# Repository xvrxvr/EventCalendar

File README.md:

# EventCalendar
Event Calendar Project

This project is a custom hardware device (with an ESP32 microcontroller, an LCD, a fingerprint sensor, and a bunch of solenoids that are used as control locks for a set of small doors)
Each door closes a separate box with some kind of gift.
The user must solve some kind of puzzle to open the door.

## Project Contents

Directory Contents:

* 3D contains a 3D model for the panel around the LCD
* sch - Schematic. The PCB version is outdated at this point (some schematic changes were made after the PCB was provided). There are also 2 schematics:
  * **ev_cal** - The calendar itself
  * **vboost** - Voltage boost for the solenoids (it is connected instead of L1)
* soft - Software. 6 directories included:
  * expr_quest - Prototype (in Python) for benchmark testing
  * firmware - Firmware (VS Code + IDF plugin)
  * sg - Character generator scripts
  * tst - Hardware test (VS Code + IDF plugin)
  * bloader - OTA loader (OTA is also supported in the main software)
  * ext_logger - External logger client. The external logging system is currently under development. It allows forwarding all internal UART messages to a remote TCP server. This system (with OTA capability) allows creating and debugging new software versions without special software hardware.
* spice - Spice mode for the voltage amplifier

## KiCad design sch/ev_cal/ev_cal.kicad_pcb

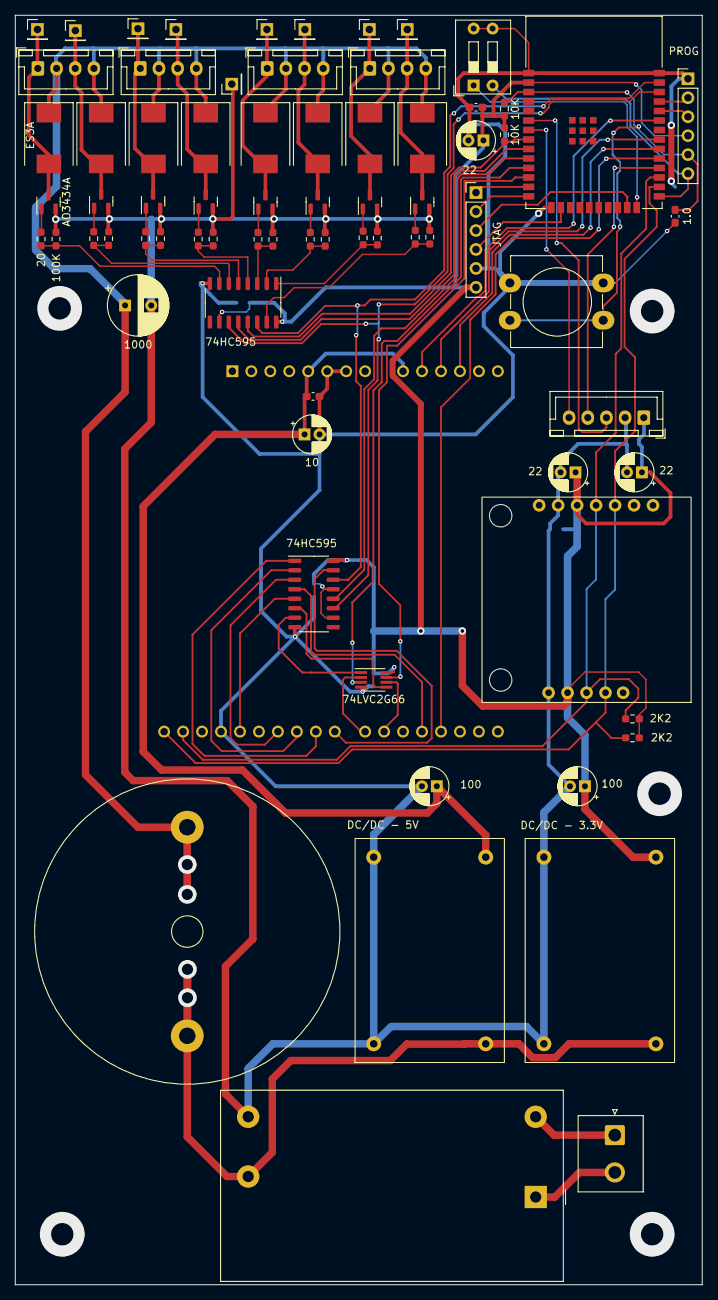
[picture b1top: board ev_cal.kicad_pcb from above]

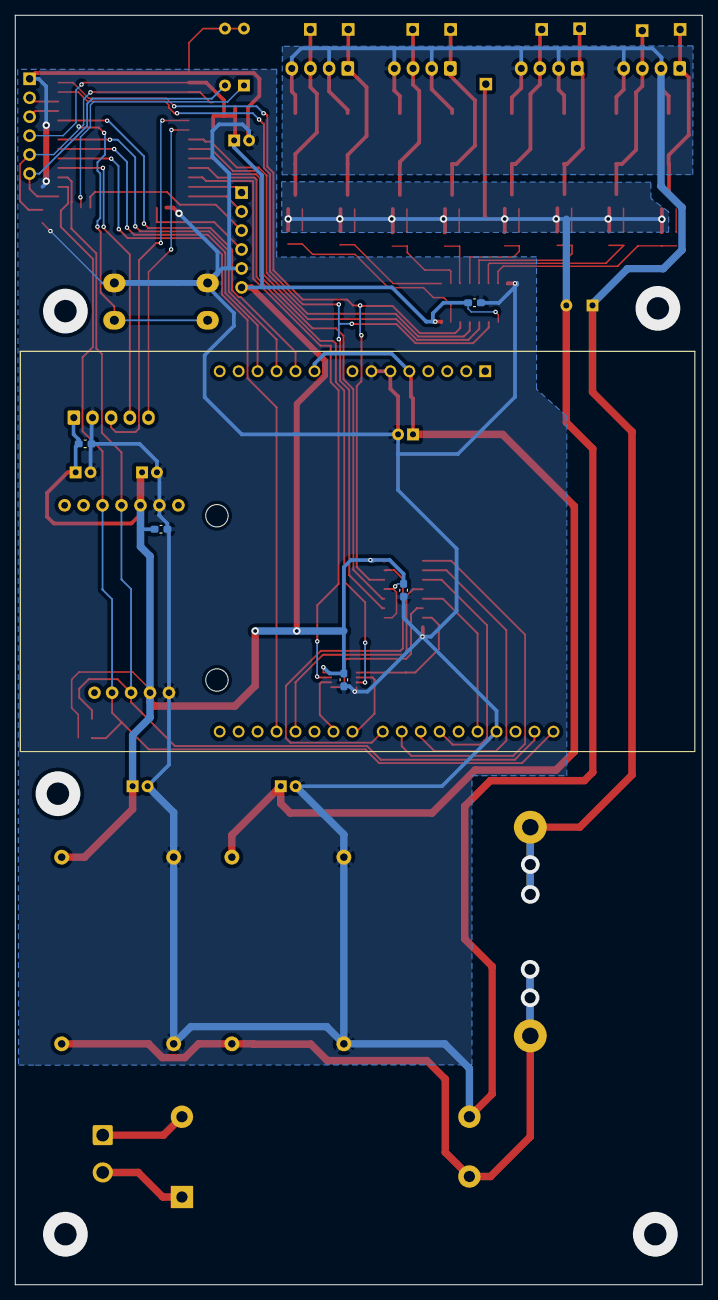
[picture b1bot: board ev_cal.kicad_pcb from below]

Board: 2 copper layers, 92.0 x 170.0 mm, 80 parts (6 on the bottom side), 66 nets.

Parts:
C1: 10; CP_Radial_D5.0mm_P2.00mm
C2, C7, C10: 22; CP_Radial_D5.0mm_P2.00mm
C3, C9, C11, C12, C13, C14, C15: 0.1; C_0603_1608Metric_Pad1.08x0.95mm_HandSolder
C4: 1.0; C_0603_1608Metric_Pad1.08x0.95mm_HandSolder
C5, C6: 100; CP_Radial_D5.0mm_P2.00mm
C8: 1000; CP_Radial_D8.0mm_P3.50mm
D1, D2, D3, D4, D5, D6, D7, D8: ES3A; D_SMC
J1: JTAG; PinHeader_1x06_P2.54mm_Vertical
J2: PROG; PinHeader_1x06_P2.54mm_Vertical
J3, J4, J5, J6: Conn_01x04_Male; JST_XH_B4B-XH-A_1x04_P2.50mm_Vertical
J11: Conn_01x01_Male; PinHeader_1x01_P2.54mm_Vertical
J12, J13, J14, J15, J16, J17, J18, J19: Conn_01x01_Female; PinHeader_1x01_P2.54mm_Vertical
L1: 10mH; L_Radial_D40.6mm_P27.94mm_Vishay_IHB-4
P1: Conn_WallPlug; JST_NV_B02P-NV_1x02_P5.00mm_Vertical
PS1: IRM-10-12; Converter_ACDC_MeanWell_IRM-10-xx_THT
Q1, Q2, Q3, Q4, Q5, Q6, Q7, Q8: AO3434A; SOT-23
R1, R2: 10K; R_0603_1608Metric_Pad0.98x0.95mm_HandSolder
R3, R4: 2K2; R_0603_1608Metric_Pad0.98x0.95mm_HandSolder
R5, R7, R9, R11, R13, R15, R17, R19: 100K; R_0603_1608Metric_Pad0.98x0.95mm_HandSolder
R6, R8, R10, R12, R14, R16, R18, R20: 20; R_0603_1608Metric_Pad0.98x0.95mm_HandSolder
SW1: SW_Push; SW_PUSH-12mm_Wuerth-430476085716
SW2: SW_DIP_x02; SW_DIP_SPSTx02_Slide_9.78x7.26mm_W7.62mm_P2.54mm
U1: ESP32-WROOM-32E-N8
U2: DC/DC - 5V; DD_DC
U3: DC/DC - 3.3V; DD_DC
U4: R503; JST_XH_B5B-XH-A_1x05_P2.50mm_Vertical
U5: HW-111
U6, U7: 74HC595; SO-16_3.9x9.9mm_P1.27mm
U8: 74LVC2G66; SSOP-8_2.95x2.8mm_P0.65mm
U9: LCD

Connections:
+3.3V: C2.1, C3.1, C6.1, C7.1, C9.1, C10.1, C11.1, C12.1, C13.1, C14.1, J1.6, J2.4, R1.1, R2.2, R3.1, R4.1, U1.2 (3V3), U3.3 (OUT+), U4.1 (DC3.3V_(Red)/6), U5.4 (VCC), U5.10 (VCC), U6.10 (~SRCLR), U6.16 (VCC), U7.10 (~SRCLR), U7.13 (~OE), U7.16 (VCC), U8.8 (+3.3V)
+5V: C1.1, C5.1, C15.1, U2.3 (OUT+), U9.23 (+5V), U9.27 (RD)
+12V: C8.1, D1.1 (K), D2.1 (K), D3.1 (K), D4.1 (K), D5.1 (K), D6.1 (K), D7.1 (K), D8.1 (K), J3.2, J3.4, J4.2, J4.4, J5.2, J5.4, J6.2, J6.4, L1.1
/CLK: U1.36 (IO22), U6.11 (SRCLK), U7.11 (SRCLK)
/DI: U1.37 (IO23), U6.14 (SER), U7.14 (SER)
/EN: C4.1, J2.5, R1.2, SW1.2, U1.3 (EN)
/FP_RXD: U1.28 (IO17), U4.4 (RXD_(Green))
/FP_TXD: U1.6 (IO34), U4.3 (TXD_(Yellow))
/FP_WAKEUP: U1.7 (IO35), U4.5 (WAKEUP_(Blue))
/LCD-CS: U1.10 (IO25), U7.12 (RCLK)
/LCD-SW1: U1.12 (IO27), U8.7
/LCD-SW2: U1.11 (IO26), U8.3
/LCD_BL: U1.29 (IO5), U9.15 (LCD-BL)
/LCD_LATCH: U1.30 (IO18), U9.30 (CS)
/RS/X-: U1.31 (IO19), U9.29 (RS/X-)
/S1/I: R5.1, R6.1, U6.15 (QA)
/S1/O: D1.2 (A), J3.3, J12.1, Q1.3 (D)
/S2/I: R7.1, R8.1, U6.1 (QB)
/S2/O: D2.2 (A), J3.1, J13.1, Q2.3 (D)
/S3/I: R9.1, R10.1, U6.2 (QC)
/S3/O: D3.2 (A), J4.3, J14.1, Q3.3 (D)
/S4/I: R11.1, R12.1, U6.3 (QD)
/S4/O: D4.2 (A), J4.1, J15.1, Q4.3 (D)
/S5/I: R13.1, R14.1, U6.4 (QE)
/S5/O: D5.2 (A), J5.3, J16.1, Q5.3 (D)
/S6/I: R15.1, R16.1, U6.5 (QF)
/S6/O: D6.2 (A), J5.1, J17.1, Q6.3 (D)
/S7/I: R17.1, R18.1, U6.6 (QG)
/S7/O: D7.2 (A), J6.3, J18.1, Q7.3 (D)
/S8/I: R19.1, R20.1, U6.7 (QH)
/S8/O: D8.2 (A), J6.1, J19.1, Q8.3 (D)
/SCL: R3.2, U1.26 (IO4), U5.2 (SCL), U5.8 (SCL), U9.1 (SCL)
/SDA: R4.2, U1.27 (IO16), U5.3 (SDA), U5.9 (SDA), U9.2 (SDA)
/SOLENOID_CS: U1.9 (IO33), U6.12 (RCLK)
/SOLENOID_OE: R2.1, U1.8 (IO32), U6.13 (~OE)
/TCK: J1.4, U1.16 (IO13)
/TDI: J1.2, U1.14 (IO12)
/TDO: J1.3, U1.23 (IO15)
/TMS: J1.1, U1.13 (IO14)
/WR/Y+: U1.33 (IO21), U9.28 (WR/Y+)
GND: C1.2, C2.2, C3.2, C4.2, C5.2, C6.2, C7.2, C8.2, C9.2, C10.2, C11.2, C12.2, C13.2, C14.2, C15.2, J1.5, J2.1, J11.1, PS1.3 (-Vo), Q1.2 (S), Q2.2 (S), Q3.2 (S), Q4.2 (S), Q5.2 (S), Q6.2 (S), Q7.2 (S), Q8.2 (S), R5.2, R7.2, R9.2, R11.2, R13.2, R15.2, R17.2, R19.2, SW1.1, SW2.3, SW2.4, U1.1 (GND), U1.15 (GND), U1.38 (GND), U2.2 (IN-), U2.4 (OUT-), U3.2 (IN-), U3.4 (OUT-), U4.2 (GND_(Black)), U5.5 (GND), U5.11 (GND), U6.8 (GND), U7.8 (GND), U8.4 (GND), U9.4 (GND), U9.24 (GND), U9.25 (GND)
unnamed: J2.2, U1.35 (TXD0)
unnamed: J2.3, U1.34 (RXD0)
unnamed: J2.6, SW2.2, U1.25 (IO0)
unnamed: L1.2, PS1.4 (+Vo), U2.1 (IN+), U3.1 (IN+)
unnamed: P1.1 (AC_P), PS1.2 (AC/L)
unnamed: P1.2 (AC_N), PS1.1 (AC/N)
unnamed: Q1.1 (G), R6.2
unnamed: Q2.1 (G), R8.2
unnamed: Q3.1 (G), R10.2
unnamed: Q4.1 (G), R12.2
unnamed: Q5.1 (G), R14.2
unnamed: Q6.1 (G), R16.2
unnamed: Q7.1 (G), R18.2
unnamed: Q8.1 (G), R20.2
unnamed: SW2.1, U1.24 (IO2)
unnamed: U7.1 (QB), U9.9 (DB1)
unnamed: U7.2 (QC), U9.8 (DB2)
unnamed: U7.3 (QD), U9.7 (DB3)
unnamed: U7.4 (QE), U9.14 (DB4)
unnamed: U7.5 (QF), U9.5 (DB5)
unnamed: U7.6 (QG), U8.5
unnamed: U7.7 (QH), U8.1
unnamed: U7.15 (QA), U9.10 (DB0)
unnamed: U8.2, U9.11 (DB7/Y-)
unnamed: U8.6, U9.12 (DB6/X+)

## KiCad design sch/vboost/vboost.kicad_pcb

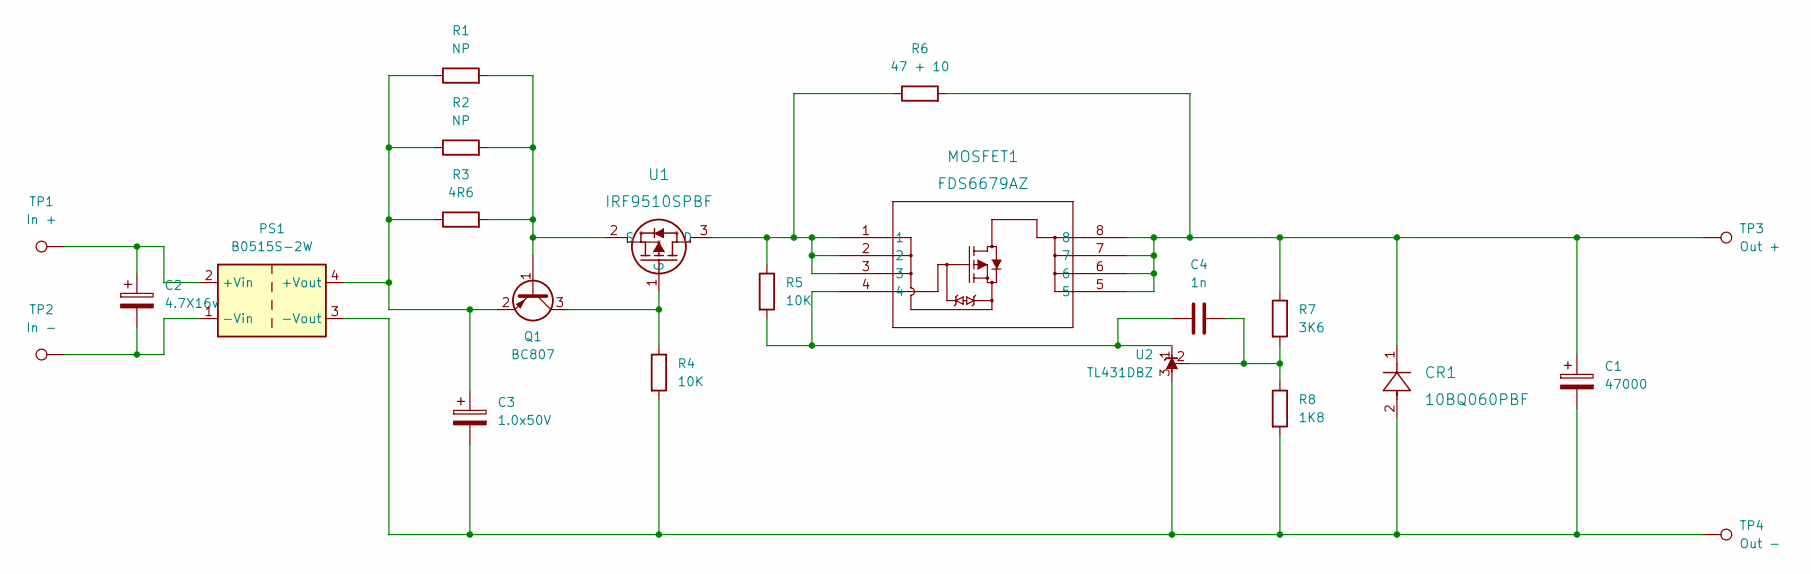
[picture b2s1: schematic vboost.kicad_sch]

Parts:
C1: 47000; CP_Radial_D35.0mm_P10.00mm_SnapIn
C2: 4.7X16v; CP_Radial_D5.0mm_P2.00mm
C3: 1.0x50V; CP_Radial_D5.0mm_P2.00mm
C4: 1n; C_0805_2012Metric_Pad1.18x1.45mm_HandSolder
CR1: 10BQ060PBF; DIODE_SMB_VIS-M
MOSFET1: FDS6679AZ; SOIC8_751EB_ONS-M
PS1: B0515S-2W
Q1: BC807; SOT-23
R1, R2: NP; R_0805_2012Metric_Pad1.20x1.40mm_HandSolder
R3: 4R6; R_0805_2012Metric_Pad1.20x1.40mm_HandSolder
R4, R5: 10K; R_0805_2012Metric_Pad1.20x1.40mm_HandSolder
R6: 47 + 10; R2
R7: 3K6; R_0805_2012Metric_Pad1.20x1.40mm_HandSolder
R8: 1K8; R_0805_2012Metric_Pad1.20x1.40mm_HandSolder
TP1: In +; TP1
TP2: In -; TP1
TP3: Out +; TP1
TP4: Out -; TP1
U1: IRF9510SPBF; D2PAK_VIS-M
U2: TL431DBZ; SOT-23

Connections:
unnamed: C1.1, CR1.1, MOSFET1.5, MOSFET1.6, MOSFET1.7, MOSFET1.8, R6.2, R7.1, TP3.1
unnamed: C1.2, C3.2, CR1.2, PS1.3 (-Vout), R4.2, R8.2, TP4.1, U2.3 (A)
unnamed: C2.1, PS1.2 (+Vin), TP1.1
unnamed: C2.2, PS1.1 (-Vin), TP2.1
unnamed: C3.1, PS1.4 (+Vout), Q1.2 (E), R1.1, R2.1, R3.1
unnamed: C4.1, MOSFET1.4, R5.2, U2.1 (K)
unnamed: C4.2, R7.2, R8.1, U2.2 (REF)
unnamed: MOSFET1.1, MOSFET1.2, MOSFET1.3, R5.1, R6.1, U1.3 (D)
unnamed: Q1.1 (B), R1.2, R2.2, R3.2, U1.2 (S)
unnamed: Q1.3 (C), R4.1, U1.1 (G)

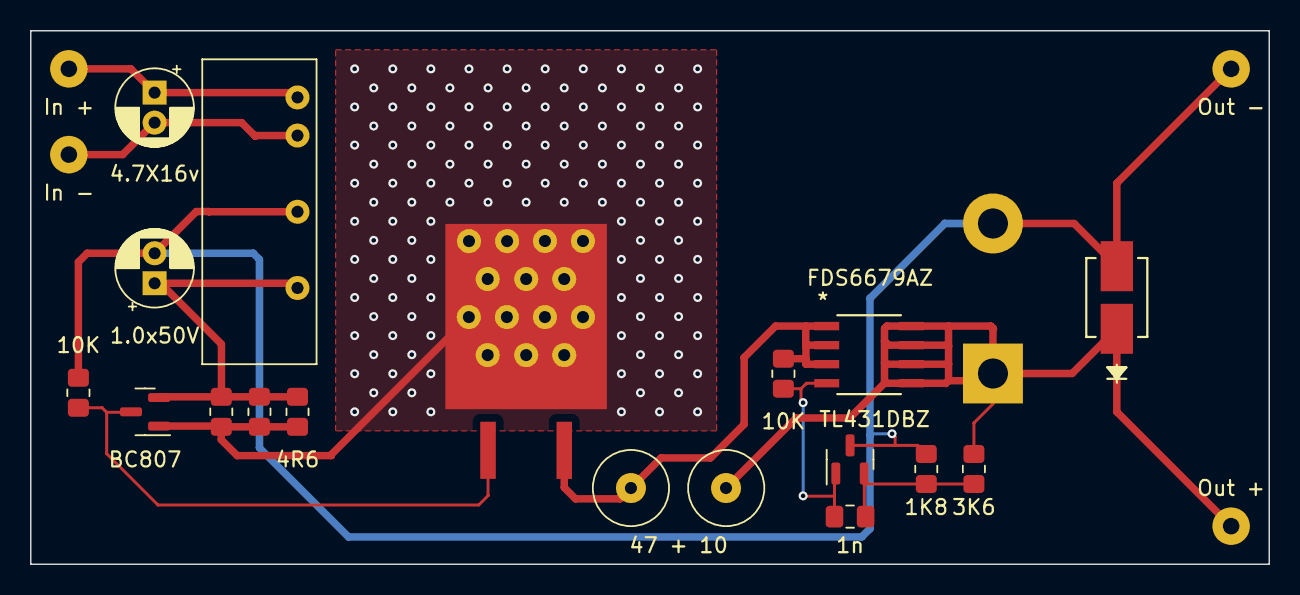
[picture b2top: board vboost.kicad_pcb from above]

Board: 2 copper layers, 82.5 x 35.6 mm, 22 parts (1 on the bottom side), 10 nets.

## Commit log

2023-09-09 Initial version
2023-09-18 Added setup and wifi modules
2023-09-29 Added WEB servers
2023-10-15 Fixed EEPROM access Fixed WiFi code Running WEb services
2023-10-18 Added WEB proto
2023-10-19 Added more WEB pages
2023-10-20 Added script for generating WEB files mux
2023-10-21 Updated script output
2023-10-23 Small fixes
2023-10-23 Added conditional markup to WEB pages and proto file for WEB substitution definition
2023-10-24 Added WebVarEncoder file and update generation script to produce it
2023-10-24 Added WEB gadgets
2023-10-24 Cache-Control header added
2023-10-25 Compiled version (CDN files assed to builtin WEB server)
2023-10-28 WEB server contents runs
2023-10-29 Added proto of Activity manager
2023-10-29 Cont development of Activity manager
2023-10-29 Update2
2023-10-30 Continue implementation of AJAX web_actions
2023-10-30 Added stubs for AJAX requests (project in compilable state)
2023-10-31 Small headers refactor + pin attached HW common class
2023-10-31 All HW Inputs implemented
2023-11-02 Debugging of Activity in progress
2023-11-02 Activity debug - separated Activity runs. Next step - override and borrow
2023-11-03 Borrowed/overrided Activities works
2023-11-04 BG image scan/load/show added
2023-11-04 Adjust Print buffers in heap
2023-11-08 Started Box Draw implementation
2023-11-11 Box draw is working.
2023-11-13 Add proto of Text Box formatter
2023-11-14 Update of Box Showing support
2023-11-16 TextBoxDraw moved to *.cpp form
2023-11-16 Challenge processing WEB files updated
2023-11-20 TextDraw runs
2023-11-20 Aux functions implemented
2023-11-21 Added editor for FG (buisness logic part)
2023-11-21 Added buisness logic for FP View WEB page
2023-11-22 Websocket support added
2023-11-23 Added implementation of WEB vars. Started implementation of Chellenge Mgr
2023-11-24 AJAX entries implemented
2023-11-24 Activated GDB Stub
2023-11-25 Added support for time sync via SNTP
2023-11-25 Interactive::entry() added to Main - ready to debug
2023-11-25 Extend FP Characters in template to 6
2023-11-25 Update WEB part for 6 FG characters in Template
2023-11-25 Small sync & fix
2023-11-26 Converted Expression Challenge from Python to C++
2023-11-27 Interactive part partially works
2023-11-28 Interactive setup is working. Starting doors and game setup debuggoing
2023-11-29 Added local animated Panel in FG Editor
2023-11-30 Interactive part working (all)
2023-12-01 Added Grid manager (keyboard, 15 game, Door handle, etc)
2023-12-02 Added keyboard manager and Keyboard layouts
2023-12-04 Keyboard manager running
2023-12-04 Prepare to DoorManager
2023-12-05 DoorManager working. Added Stat WEB page (memory + tasks)
2023-12-06 Fix for DoorOpen module
2023-12-06 Equatuion Challenge core implemented
2023-12-07 Multiselect implemented
2023-12-07 Butify Equation Challenge
2023-12-07 CmakeLists updated - moved to GLOB lists (vs explicitly specified cpp files)
2023-12-07 Challenge file reading and parsing added
2023-12-08 Riddle challenge implemented
2023-12-09 Butify riddle challenge
2023-12-10 game 15 ready to debug
2023-12-11 Game 15 running
2023-12-11 Tile game added
2023-12-12 Added animation to Tile game and 15 Game
2023-12-12 Added auto solver to Tile Game
2023-12-12 force BG set for help icon
2023-12-13 Added challenged to Interactive - Final version (ready to debug)
2023-12-14 Almost ready (autosolver for 15 Game not ready yet)
2023-12-24 Lasst fixes
2023-12-25 Fizzy compare fix. Added AP/Sta Info message box
2023-12-25 Added support for DOS/UTF8 mix in UTF8 encoded strings. Added print of User name in entry messages.
2025-01-15 Config changed
2025-01-19 Added (not yet tested) Backup/restore support
2025-02-02 Added support for data backup
2025-02-04 Added OTA support
2025-02-05 Added FW update in GUI
2025-02-08 Multiple fixes
2025-02-10 Started support for local (on-device) Gift Loading
2025-02-10 Added FW update bat files
2025-02-24 Running (still in debug) local LCD Gift loading action
2025-02-25 Running local LCD Gift loading action - Toggle Buttons part
2025-02-28 Added DoorsManager and LCD based Gift Loading (not tested yet)
2025-03-04 Updated LCD gifts doors manager
2025-03-05 LCD gifts doors manager working
2025-03-08 Tested in real life
2025-03-08 Fixed 'close' icon on Gift Get LCD screen'
2025-03-08 Started implementation of Remote logging system
2025-03-09 Added module for Remote Log
2025-04-20 Added external logger
2025-04-26 ExtLog system update - ready to run
2025-04-26 Readme updated
2025-04-26 Added PDF of schematic
2025-04-26 PDF moved to sch dir
2025-04-27 Added CoreDump support

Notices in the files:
parts and their libraries:
Copyright 2021 Accelerated Designs. All rights reserved.
